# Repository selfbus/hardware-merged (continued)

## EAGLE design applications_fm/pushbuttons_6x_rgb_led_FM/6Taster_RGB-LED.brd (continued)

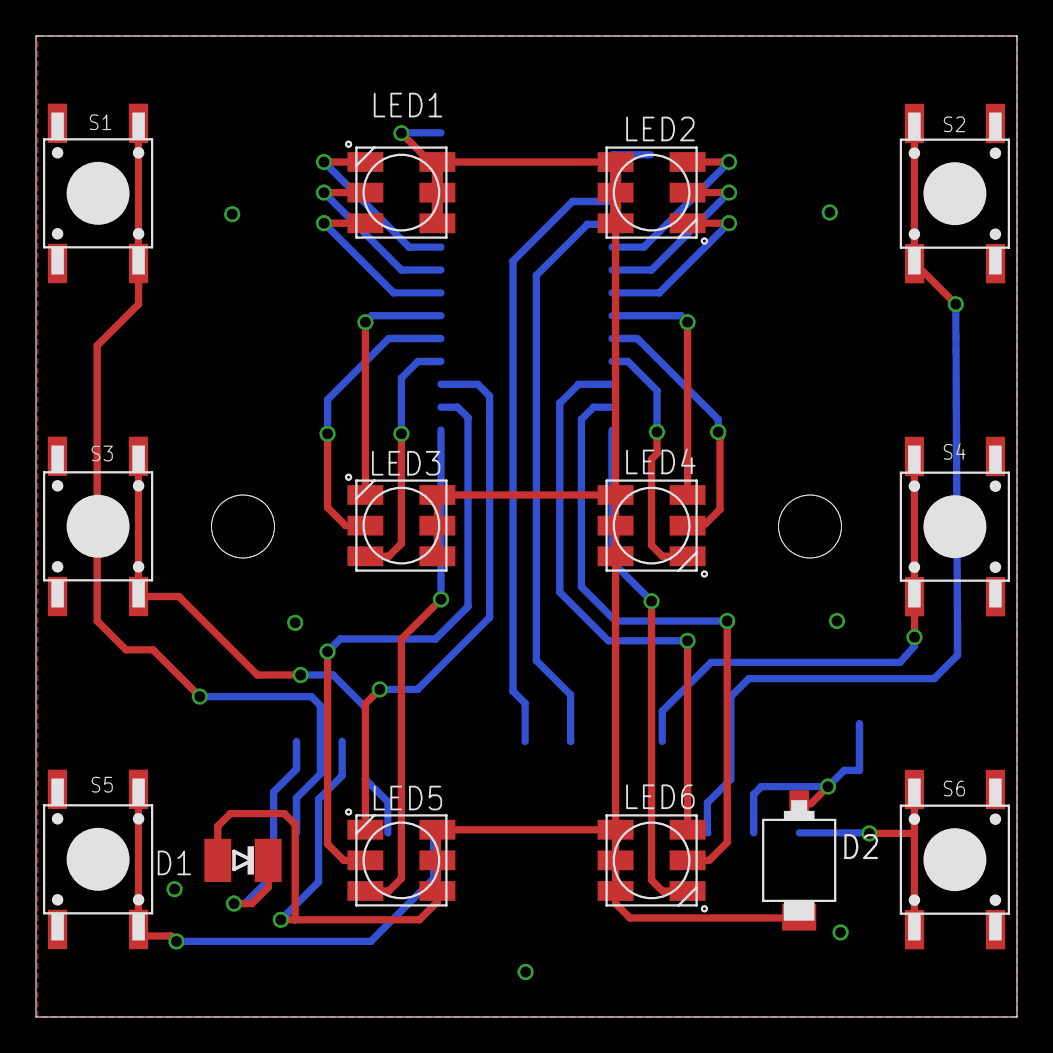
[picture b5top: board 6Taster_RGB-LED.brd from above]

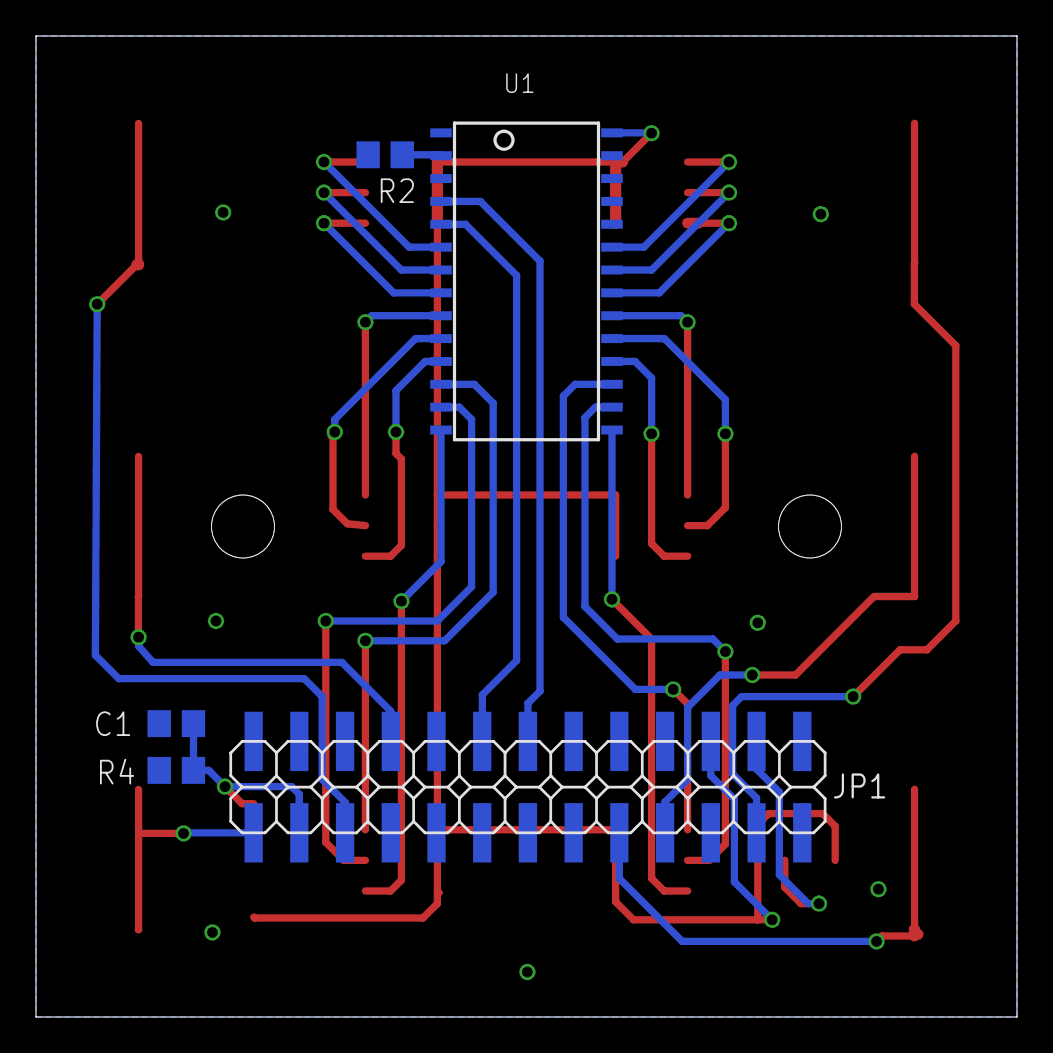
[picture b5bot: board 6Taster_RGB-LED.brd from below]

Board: 2 copper layers, 54.5 x 54.5 mm, 19 parts (5 on the bottom side), 31 nets.

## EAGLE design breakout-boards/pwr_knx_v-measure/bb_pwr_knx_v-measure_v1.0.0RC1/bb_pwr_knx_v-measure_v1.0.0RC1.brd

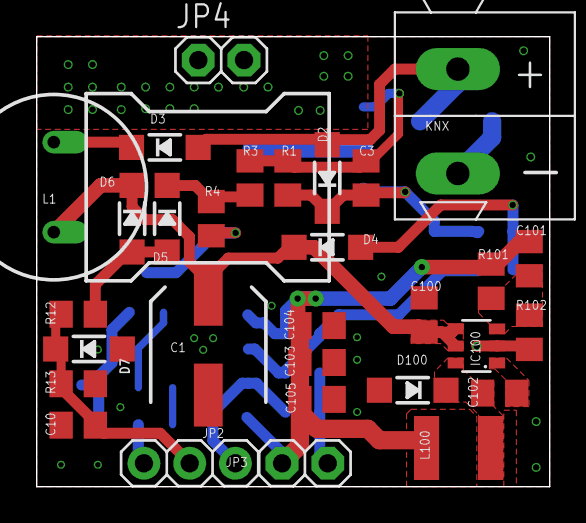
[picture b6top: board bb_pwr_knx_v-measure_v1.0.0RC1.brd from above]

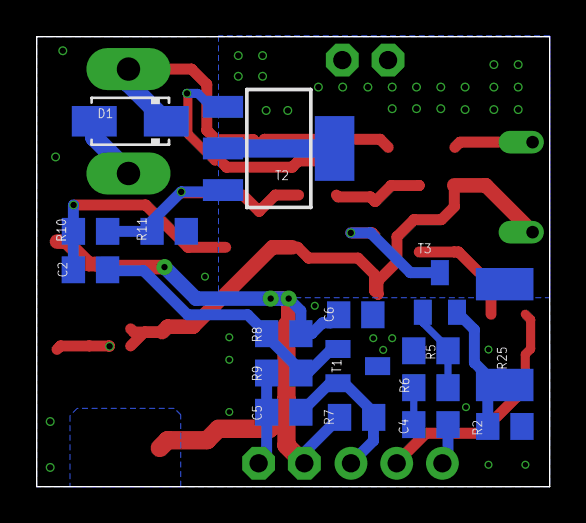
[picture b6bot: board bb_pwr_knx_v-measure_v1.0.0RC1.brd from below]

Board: 2 copper layers, 28.5 x 25.0 mm, 47 parts (17 on the bottom side), 22 nets.

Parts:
C1: 100uF 35V; SANYO-OSCON_SMD_C6
C2, C6, C10, C104: 100nF; C0805
C3, C4: 10nF; C0805
C5: 100pF; C0805
C100: 4.7uF 50V; C0805
C101: 470nF; C0805
C102: 15nF; C0805
C103, C105: 47uF 10V; C0805
D1: SMAJ40CA; DO214AC
D2, D3, D4, D5: 1N4148; SOD-123
D6: 7V5; SOD-123
D7: DDZ9685; SOD-123
D100: MBRS1100; SOD-123
IC100: BD9G101; SOT23-6
JP2: 1X03
JP3, JP4: 1X02
KNX: WAGO-243-211
L1: 150mH; BS11
L100: 4.7uH; L4532P
R1, R3: 1k; R0805
R2: 5R6; R0805
R4: 2k2; R0805
R5, R9, R11: 100k; R0805
R6: 5k6; R0805
R7, R10: 10k; R0805
R8: 82k; R0805
R12: 43k; R0805
R13: 6,2k; R0805
R25: 24R 2512 1.0W; R2512
R101: 1k6; R0805
R102: 470R; R0805
T1: BC856; SOT23-BEC
T2: BCP52; SOT223
T3: BC847; SOT23

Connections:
+3V3: C6.2, C101.2, C103.1, C104.1, C105.1, JP3.1, L100.2, R7.2, R8.2, R101.2
BST: C102.2, IC100.1
BUS_V: C10.2, D7.C, JP2.2, R12.2, R13.1
EIB+: D1.C, D2.A, D3.A, KNX.1+
EIB+DIR: C3.1, D2.C, R1.1, R10.2, R11.2, T2.3
EIB_DC: C1.+, C100.2, D4.C, D6.C, IC100.4, IC100.5, L1.1
EIB_IN: C5.2, JP2.3, R7.1, T1.E
EIB_OUT: C4.2, JP2.1
FB: C101.1, IC100.3, R101.1, R102.2
GND: C1.-, C5.1, C6.1, C10.1, C100.1, C103.2, C104.2, C105.2, D1.A, D7.A, D100.A, IC100.2, JP3.2, KNX.2-, R2.1, R5.2, R9.1, R11.1, R13.2, R102.1, T1.C
LX: C102.1, D100.C, IC100.6, L100.1
unnamed: C2.2, D4.A, R10.1
unnamed: D3.C, L1.2
unnamed: C4.1, R6.2
unnamed: R4.1, T3.3
unnamed: R2.2, R25.1, T3.2
unnamed: JP4.1, JP4.2, R25.2, T2.2, T2.4
unnamed: R5.1, R6.1, T3.1
unnamed: C2.1, R8.1, R9.2, T1.B
unnamed: C3.2, R1.2, R3.2, T2.1
unnamed: D5.C, R3.1, R4.2
REF: D5.A, D6.A, R12.1

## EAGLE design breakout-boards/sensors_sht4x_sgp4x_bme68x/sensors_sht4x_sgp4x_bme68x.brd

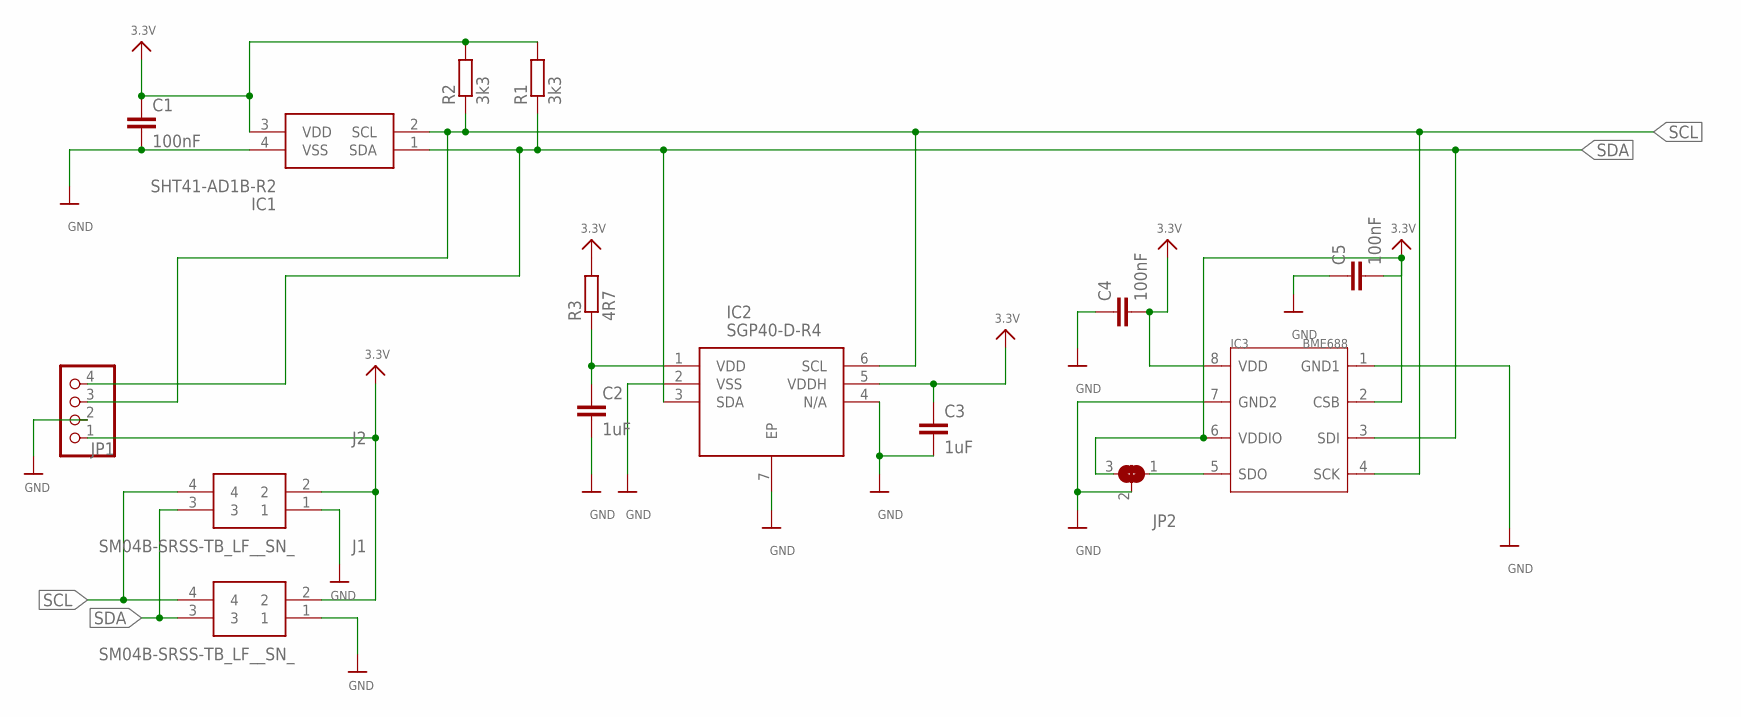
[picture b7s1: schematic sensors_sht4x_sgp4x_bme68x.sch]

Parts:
C1, C4, C5: 100nF; C0805
C2, C3: 1uF; C0805
IC1: SHT41-AD1B-R2; SHT41AD1BR2
IC2: SGP40-D-R4; SON80P244X244X95-7N
IC3: BME688; SNR8-0.8-3X3X0.93MM
J1, J2: SM04B-SRSS-TB_LF__SN_; SM04B-SRSS-TB(LFSN)
JP1: PINHD-1X4; 1X04
JP2: SOLDERJUMPER_2WAY0603; SOLDERJUMPER_2WAY_OPEN_0603
R1, R2: 3k3; R0805
R3: 4R7; R0805

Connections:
3.3V: C1.1, C3.1, C4.2, C5.2, IC1.3 (VDD), IC2.5 (VDDH), IC3.2 (CSB), IC3.6 (VDDIO), IC3.8 (VDD), J1.2, J2.2, JP1.1, JP2.3, R1.2, R2.2, R3.2
GND: C1.2, C2.2, C3.2, C4.1, C5.1, IC1.4 (VSS), IC2.2 (VSS), IC2.4 (N/A), IC2.7 (EP), IC3.1 (GND1), IC3.7 (GND2), J1.1, J2.1, JP1.2, JP2.2
unnamed: C2.1, IC2.1 (VDD), R3.1
unnamed: IC3.5 (SDO), JP2.1
SCL: IC1.2 (SCL), IC2.6 (SCL), IC3.4 (SCK), J1.4, J2.4, JP1.3, R2.1
SDA: IC1.1 (SDA), IC2.3 (SDA), IC3.3 (SDI), J1.3, J2.3, JP1.4, R1.1

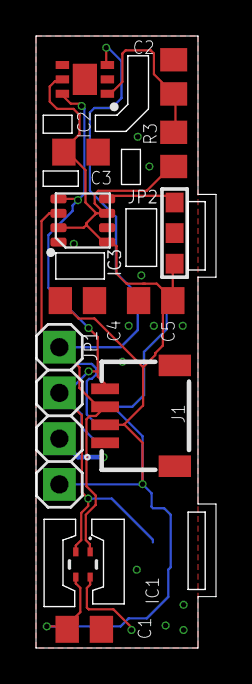
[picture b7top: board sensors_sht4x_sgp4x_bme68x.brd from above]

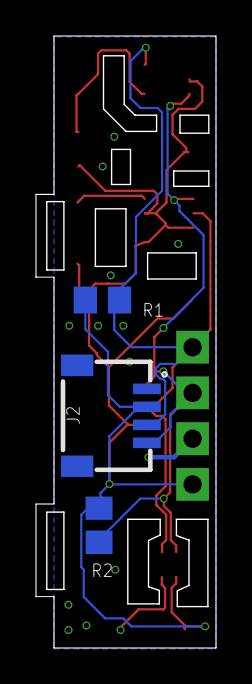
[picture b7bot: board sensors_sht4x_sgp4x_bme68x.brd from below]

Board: 2 copper layers, 10.0 x 34.0 mm, 15 parts (3 on the bottom side), 6 nets.
